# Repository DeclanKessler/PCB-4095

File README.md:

# PCB Design Coursework — PCB 4095

A portfolio of work from my ongoing PCB design class, including KiCad design files for Project 1 and assembled hardware for Project 2.

## Project 1 — KiCad Circuit and PCB Design

The [Project 1 page](projects/project-1/README.md) includes an editable KiCad schematic, PCB layout, project settings, and browser-viewable schematic and layout previews. The schematic includes TL072 operational amplifiers, LEDs, and passive components.

## Project 2 — Light-Sensing LED PCB

The photo above shows the PCB for **Project 2** of my PCB course. The circuit senses ambient room light and turns on LEDs accordingly. When the light sensor is completely covered, **two LEDs blink at 8 Hz**.

Visible board features include copper routing, surface-mount integrated circuits, resistors, capacitors, and LEDs.

**My contribution:** I completed the full project, including circuit and PCB design, etching the copper-clad board, and soldering the components.

See the [Project 2 overview](projects/project-2/README.md) for the available artifact and documentation status.

## Current status

The course is in progress. Project 1 includes KiCad source files and previews. Project 2 includes a hardware photo, functional description, and my design/fabrication/assembly contributions. Additional design explanations and measured results are still to be documented.

## Documentation plan

Each uploaded project will include its objective, my contribution, the tools used, and the available design artifacts:

- Circuit schematic and component selection
- PCB layout and relevant design constraints
- Manufacturing outputs and bill of materials, where available
- Design-review notes, revisions, and testing results

## Related work

See my [linear power supply project](https://github.com/DeclanKessler/Linear-Power-Supply) for currently available circuit simulation files and component documentation.

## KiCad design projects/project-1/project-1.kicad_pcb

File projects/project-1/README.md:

# Project 1 — KiCad Circuit and PCB Design

KiCad schematic and PCB layout files from Project 1 of my PCB design course.

## Design previews

### Schematic

[View the schematic as a PDF](previews/schematic.pdf).

### PCB layout

The schematic includes two **TL072CDR dual operational-amplifier packages**, two LEDs, resistors, capacitors, and test points. The circuit's intended function, assignment requirements, and hardware results are still to be documented.

## Source files

| File | Purpose |
| --- | --- |
| [project-1.kicad_pro](project-1.kicad_pro) | KiCad project settings |
| [project-1.kicad_sch](project-1.kicad_sch) | Editable circuit schematic |
| [project-1.kicad_pcb](project-1.kicad_pcb) | Editable PCB layout |

Open `project-1.kicad_pro` in KiCad to inspect the schematic and PCB. The included previews were exported with **KiCad 10.0.6**.

## Documentation to add

- Circuit objective and expected behavior
- My specific contribution and the assignment constraints
- Component-selection and PCB-routing decisions
- Fabrication details, board photos, and measured test results

[Return to PCB coursework](../../README.md)

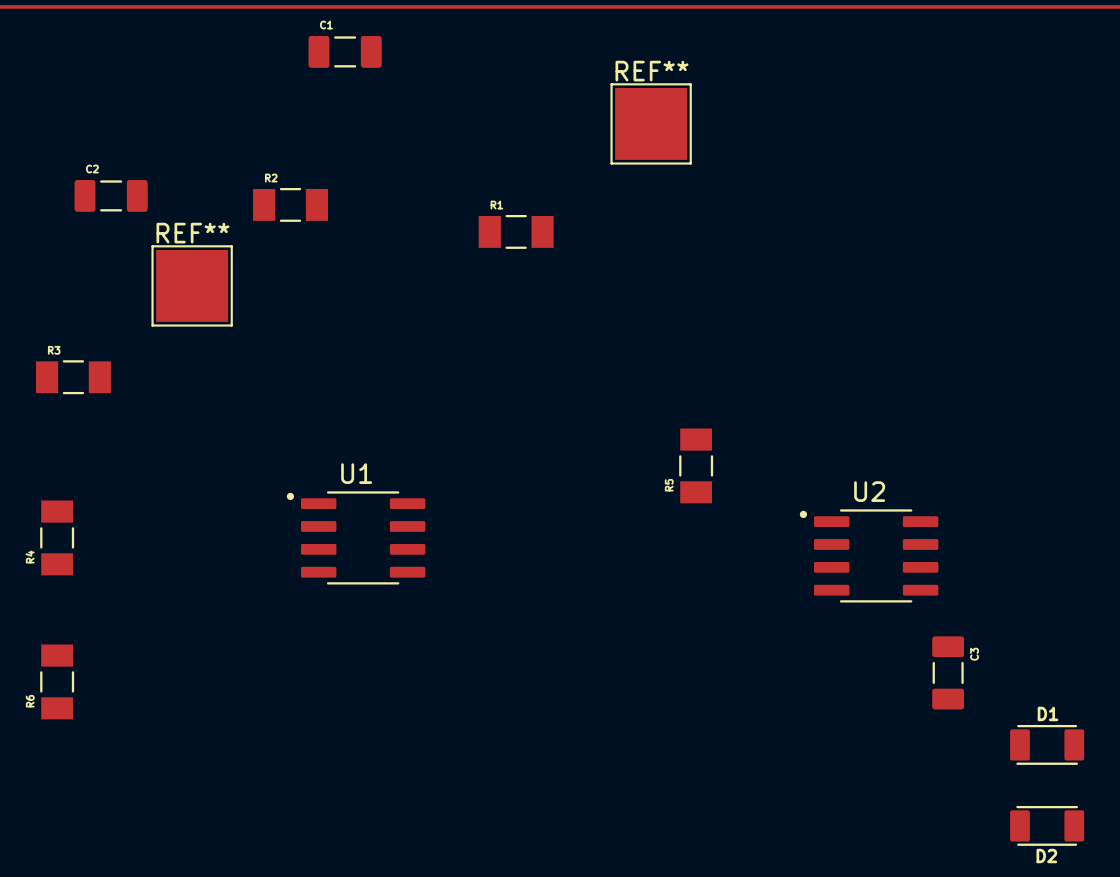
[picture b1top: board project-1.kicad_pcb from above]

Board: 2 copper layers, 13 parts (0 on the bottom side), 8 nets, no tracks yet.

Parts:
C1, C2, C3: CL31B334KBFNNNE; CAPC3216X140N
D1, D2: LTST-C230YKT; LEDC3216X110
R1, R2, R3, R4, R5, R6: RMCF1206FT10K0; RMCF1206FT10K0_RESC3216X70N
U1, U2: TL072CDR; SOIC127P599X175-8N

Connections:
unnamed: D1.C, D2.A, R6.1
unnamed: R1.1, R2.2, U1.3 (1IN+)
unnamed: C1.1, C2.1, C3.2, D1.A, D2.C, R3.2, U1.1 (1OUT), U1.2 (1IN-)
unnamed: C1.2, R1.2, U1.8 (VCC+), U2.8 (VCC+)
unnamed: C2.2, R2.1, U1.4 (VCC-), U2.4 (VCC-)
unnamed: C3.1, R5.2, U2.3 (1IN+)
unnamed: R3.1, R4.2, U2.2 (1IN-)
unnamed: R4.1, R5.1, R6.2, U2.1 (1OUT)
